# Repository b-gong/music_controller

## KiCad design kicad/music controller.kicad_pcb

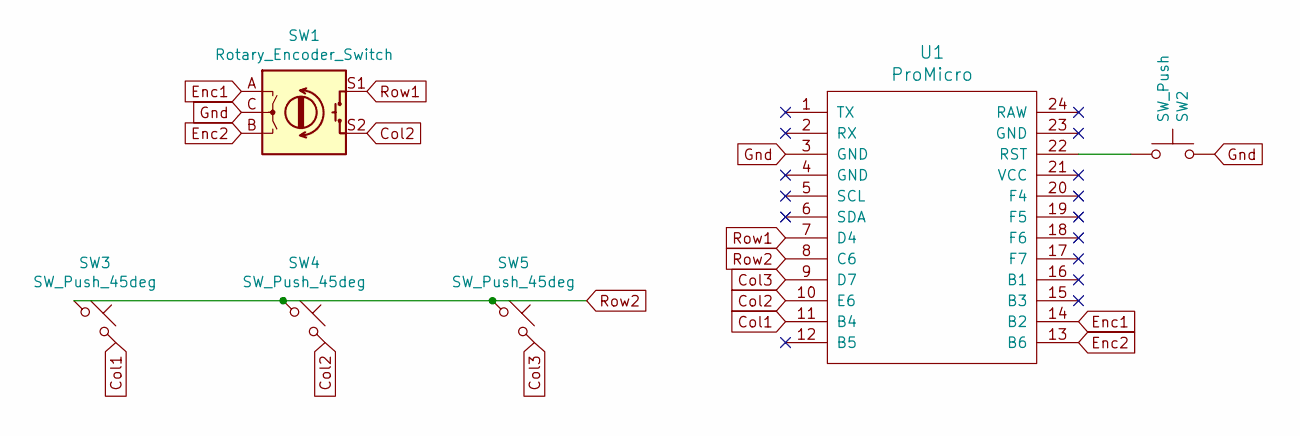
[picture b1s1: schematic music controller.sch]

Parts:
SW1: Rotary_Encoder_Switch; RotaryEncoder_Alps_EC11E-Switch_Vertical_H20mm
SW2: SW_Push; SW_PUSH_6mm
SW3, SW4, SW5: SW_Push_45deg; SW_Cherry_MX_1.00u_Plate
U1: ProMicro

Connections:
Col1: SW3.2, U1.11 (B4)
Col2: SW1.S2, SW4.2, U1.10 (E6)
Col3: SW5.2, U1.9 (D7)
Enc1: SW1.A, U1.14 (B2)
Enc2: SW1.B, U1.13 (B6)
Gnd: SW1.C, SW2.1, U1.3 (GND)
unnamed: SW2.2, U1.22 (RST)
Row1: SW1.S1, U1.7 (D4)
Row2: SW3.1, SW4.1, SW5.1, U1.8 (C6)

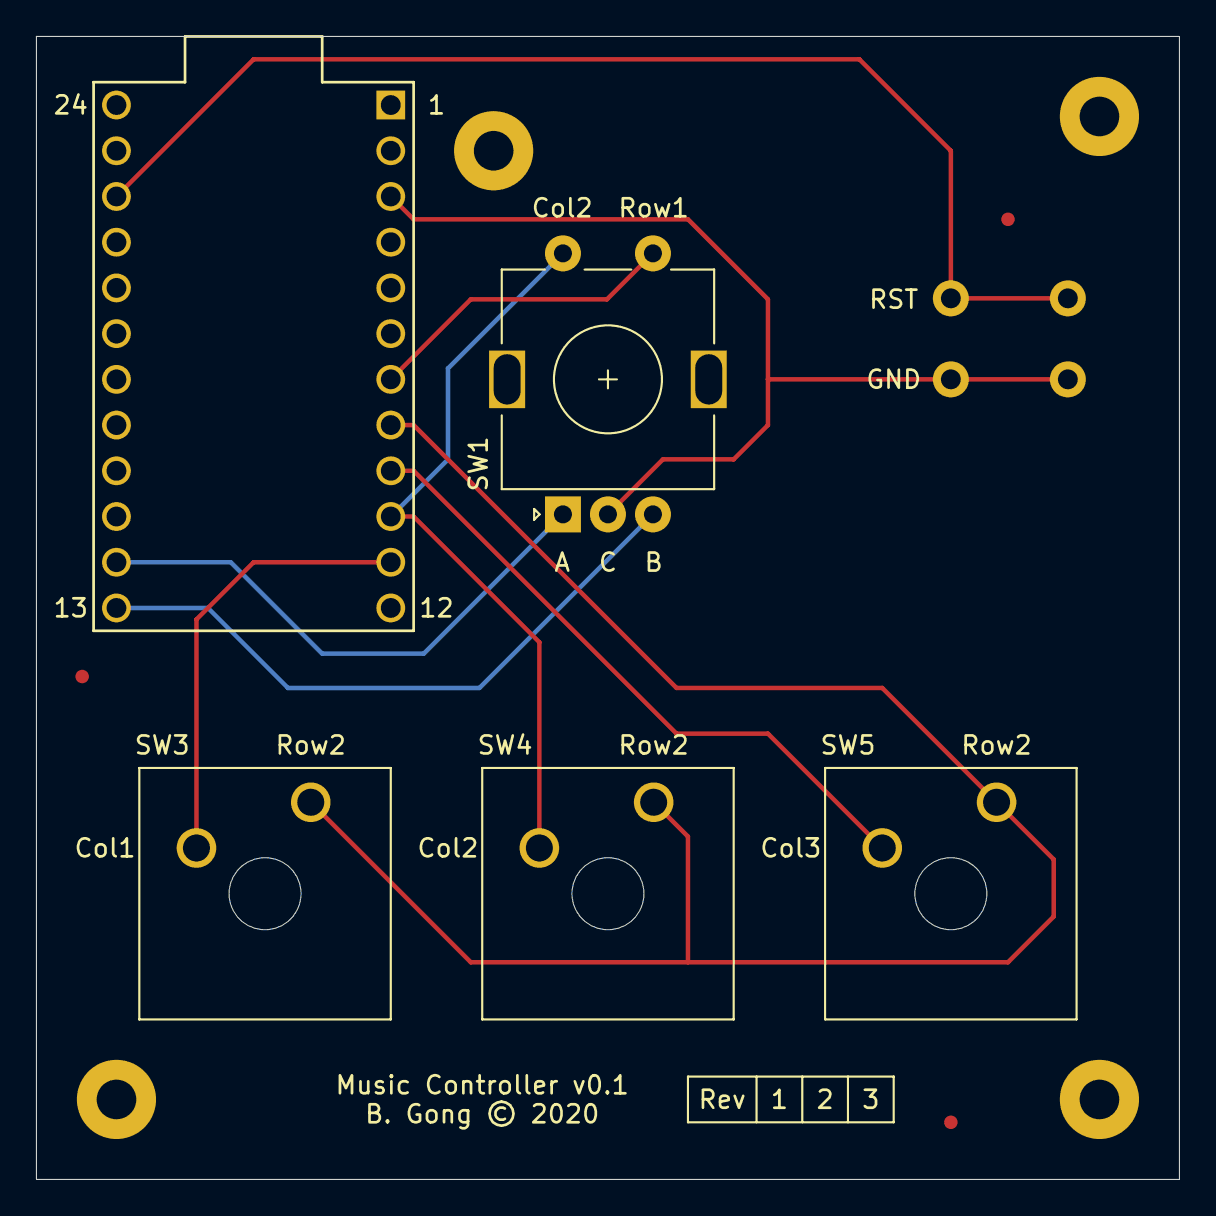
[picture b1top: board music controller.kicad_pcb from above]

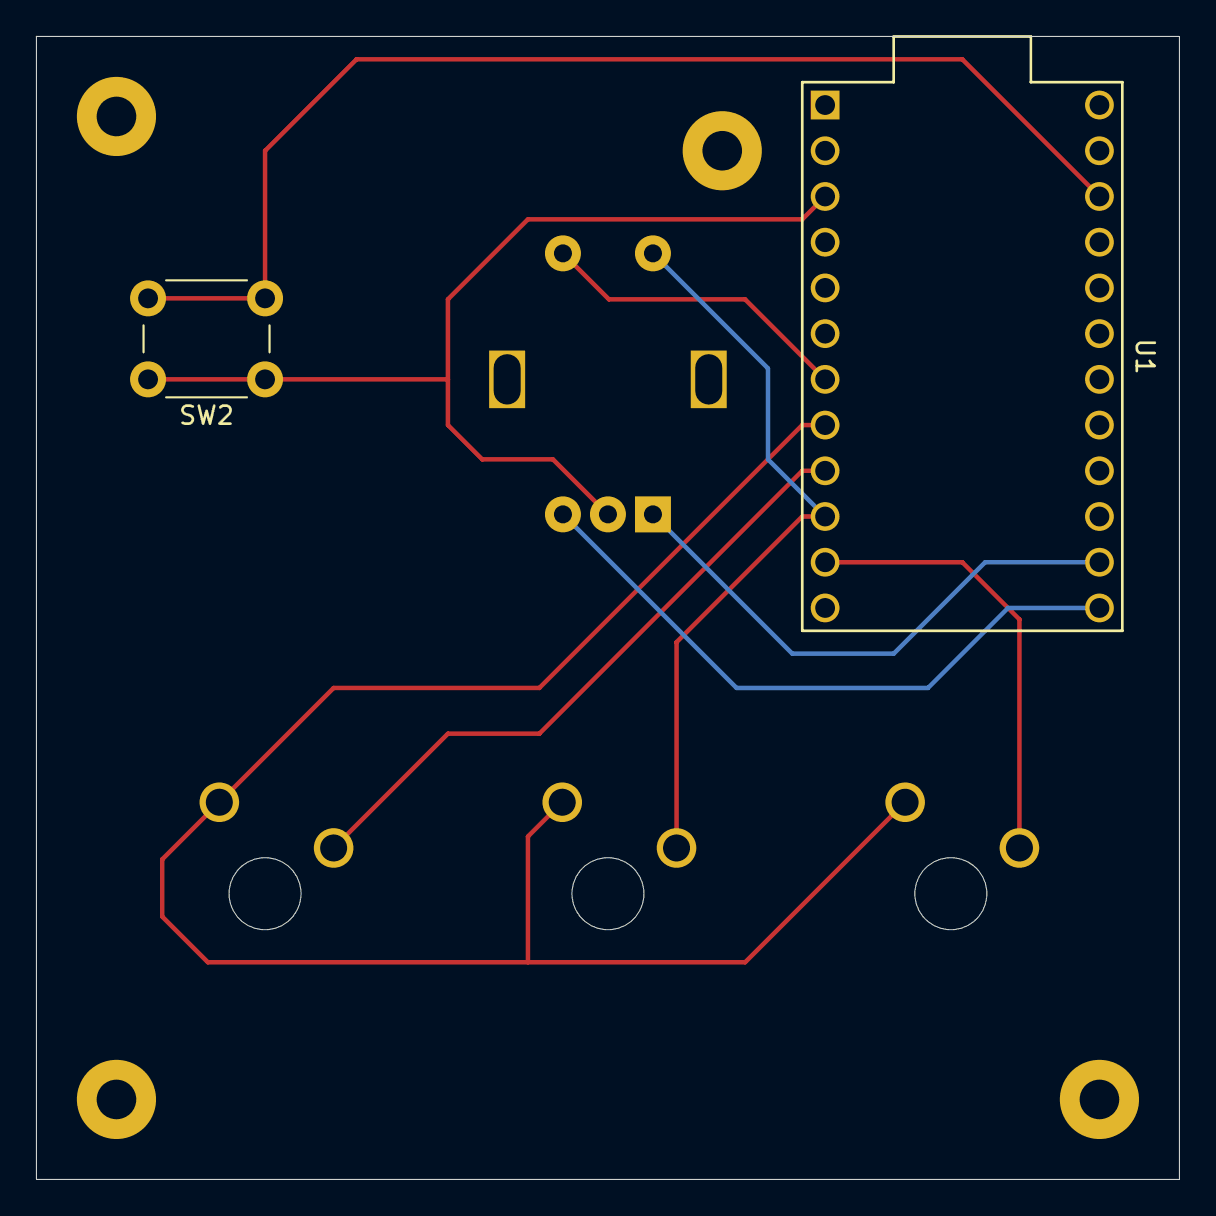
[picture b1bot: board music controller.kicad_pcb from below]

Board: 2 copper layers, 63.5 x 63.5 mm, 6 parts (2 on the bottom side), 9 nets.

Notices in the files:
kicad/music controller.kicad_pcb:
B. Gong © 2020
